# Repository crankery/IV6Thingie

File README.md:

# IV6Thingie

*This does not work yet... It may never work. I'm just goofing around*

When one learns to use a particular 7 segment display, they first make a clock.

I bought a bunch of used IV-6 (ИВ-6) 7 segment display tubes on a whim and they've been sitting in a box for years.

So, I picked out 6 of the cleanest ones and will make a clock.

## Goals

I'm not trying to invent anything new here, I'm just playing with some old electronics parts.

- Use 6 of the 49 tubes I have on hand
- Use a manufactured PCB
- Use a small PCB so it's cheap
- Use available power converter modules rather than futz with that sort of thing
- Use one of these Raspberry PI Picos I have just sitting here
- Excusively use parts that are available from our good pals at AliExpress

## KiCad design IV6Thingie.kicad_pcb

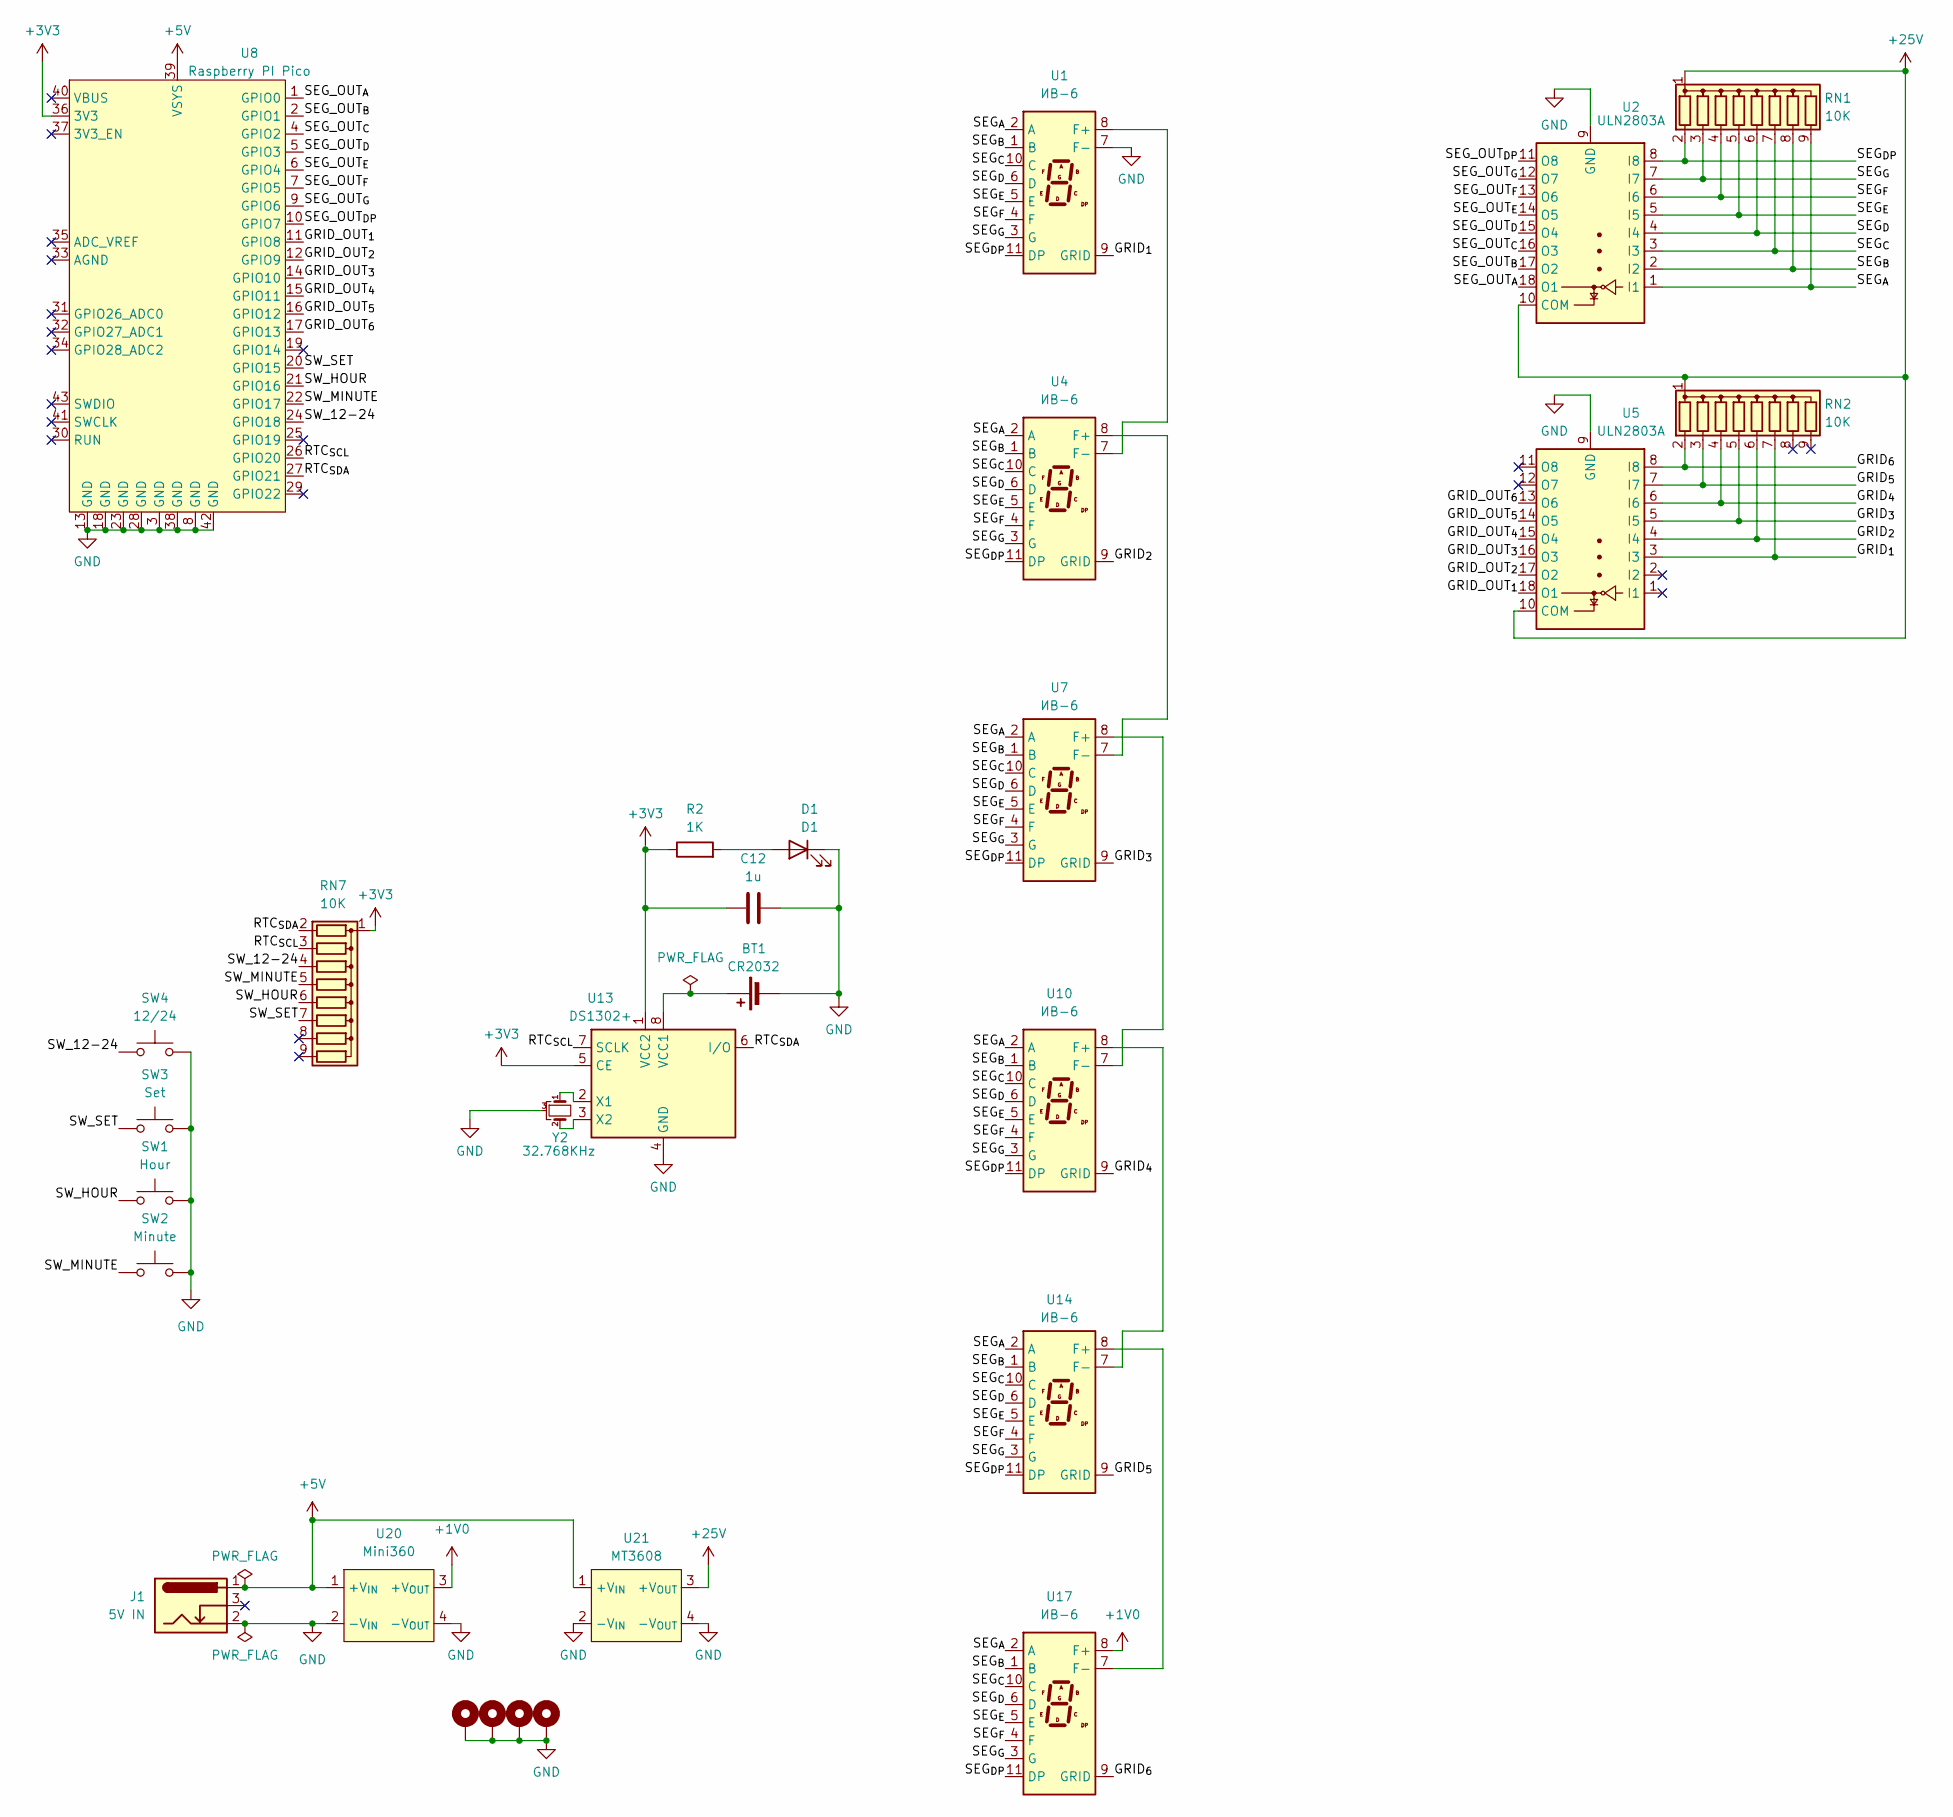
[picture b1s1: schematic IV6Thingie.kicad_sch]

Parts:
BT1: CR2032; BatteryHolder_Myoung_BS-02-Axxx006
C12: 1u; C_Disc_D4.3mm_W1.9mm_P5.00mm
D1: D1; LED_D3.0mm
H1, H2, H3, H4: MountingHole_3.2mm_M3_DIN965_Pad
J1: 5V IN; BarrelJack_Horizontal
R2: 1K; R_Axial_DIN0207_L6.3mm_D2.5mm_P7.62mm_Horizontal
RN1, RN2, RN7: 10K; R_Array_SIP9
SW1: Hour; SW_Tactile_SPST_Angled_PTS645Vx58-2LFS
SW2: Minute; SW_Tactile_SPST_Angled_PTS645Vx58-2LFS
SW3: Set; SW_Tactile_SPST_Angled_PTS645Vx58-2LFS
SW4: 12/24; SW_Tactile_SPST_Angled_PTS645Vx58-2LFS
U1, U4, U7, U10, U14, U17: ИВ-6; IV-6
U2, U5: ULN2803A; DIP-18_W7.62mm
U8: Raspberry PI Pico; RPi_Pico_SMD
U13: DS1302+; DIP-8_W7.62mm
U20: Mini360; Mini360-Module
U21: MT3608; MT3608-Module
Y2: 32.768KHz; Crystal_C26-LF_D2.1mm_L6.5mm_Horizontal_1EP_style2

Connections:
+1V0: U17.8 (F+), U20.3 (+V_{OUT})
+3V3: C12.1, R2.1, RN7.1 (common), U8.36 (3V3), U13.1 (VCC2), U13.5 (CE)
+5V: J1.1, U8.39 (VSYS), U20.1 (+V_{IN}), U21.1 (+V_{IN})
+25V: RN1.1 (common), RN2.1 (common), U2.10 (COM), U5.10 (COM), U21.3 (+V_{OUT})
/GRID_OUT_{1}: U5.18 (O1), U8.11 (GPIO8)
/GRID_OUT_{2}: U5.17 (O2), U8.12 (GPIO9)
/GRID_OUT_{3}: U5.16 (O3), U8.14 (GPIO10)
/GRID_OUT_{4}: U5.15 (O4), U8.15 (GPIO11)
/GRID_OUT_{5}: U5.14 (O5), U8.16 (GPIO12)
/GRID_OUT_{6}: U5.13 (O6), U8.17 (GPIO13)
/GRID_{1}: RN2.7 (R6), U1.9 (GRID), U5.3 (I3)
/GRID_{2}: RN2.6 (R5), U4.9 (GRID), U5.4 (I4)
/GRID_{3}: RN2.5 (R4), U5.5 (I5), U7.9 (GRID)
/GRID_{4}: RN2.4 (R3), U5.6 (I6), U10.9 (GRID)
/GRID_{5}: RN2.3 (R2), U5.7 (I7), U14.9 (GRID)
/GRID_{6}: RN2.2 (R1), U5.8 (I8), U17.9 (GRID)
/RTC_{SCL}: RN7.3 (R2), U8.26 (GPIO20), U13.7 (SCLK)
/RTC_{SDA}: RN7.2 (R1), U8.27 (GPIO21), U13.6 (I/O)
/SEG_OUT_{A}: U2.18 (O1), U8.1 (GPIO0)
/SEG_OUT_{B}: U2.17 (O2), U8.2 (GPIO1)
/SEG_OUT_{C}: U2.16 (O3), U8.4 (GPIO2)
/SEG_OUT_{DP}: U2.11 (O8), U8.10 (GPIO7)
/SEG_OUT_{D}: U2.15 (O4), U8.5 (GPIO3)
/SEG_OUT_{E}: U2.14 (O5), U8.6 (GPIO4)
/SEG_OUT_{F}: U2.13 (O6), U8.7 (GPIO5)
/SEG_OUT_{G}: U2.12 (O7), U8.9 (GPIO6)
/SEG_{A}: RN1.9 (R8), U1.2 (A), U2.1 (I1), U4.2 (A), U7.2 (A), U10.2 (A), U14.2 (A), U17.2 (A)
/SEG_{B}: RN1.8 (R7), U1.1 (B), U2.2 (I2), U4.1 (B), U7.1 (B), U10.1 (B), U14.1 (B), U17.1 (B)
/SEG_{C}: RN1.7 (R6), U1.10 (C), U2.3 (I3), U4.10 (C), U7.10 (C), U10.10 (C), U14.10 (C), U17.10 (C)
/SEG_{DP}: RN1.2 (R1), U1.11 (DP), U2.8 (I8), U4.11 (DP), U7.11 (DP), U10.11 (DP), U14.11 (DP), U17.11 (DP)
/SEG_{D}: RN1.6 (R5), U1.6 (D), U2.4 (I4), U4.6 (D), U7.6 (D), U10.6 (D), U14.6 (D), U17.6 (D)
/SEG_{E}: RN1.5 (R4), U1.5 (E), U2.5 (I5), U4.5 (E), U7.5 (E), U10.5 (E), U14.5 (E), U17.5 (E)
/SEG_{F}: RN1.4 (R3), U1.4 (F), U2.6 (I6), U4.4 (F), U7.4 (F), U10.4 (F), U14.4 (F), U17.4 (F)
/SEG_{G}: RN1.3 (R2), U1.3 (G), U2.7 (I7), U4.3 (G), U7.3 (G), U10.3 (G), U14.3 (G), U17.3 (G)
/SW_12-24: RN7.4 (R3), SW4.2, U8.24 (GPIO18)
/SW_HOUR: RN7.6 (R5), SW1.2, U8.21 (GPIO16)
/SW_MINUTE: RN7.5 (R4), SW2.2, U8.22 (GPIO17)
/SW_SET: RN7.7 (R6), SW3.2, U8.20 (GPIO15)
GND: BT1.2 (-), C12.2, D1.1 (K), H1.1, H2.1, H3.1, H4.1, J1.2, SW1.1, SW2.1, SW3.1, SW4.1, U1.7 (F-), U2.9 (GND), U5.9 (GND), U8.3 (GND), U8.8 (GND), U8.13 (GND), U8.18 (GND), U8.23 (GND), U8.28 (GND), U8.38 (GND), U8.42 (GND), U13.4 (GND), U20.2 (-V_{IN}), U20.4 (-V_{OUT}), U21.2 (-V_{IN}), U21.4 (-V_{OUT}), Y2.3
unnamed: BT1.1 (+), U13.8 (VCC1)
unnamed: D1.2 (A), R2.2
unnamed: U1.8 (F+), U4.7 (F-)
unnamed: U4.8 (F+), U7.7 (F-)
unnamed: U10.8 (F+), U14.7 (F-)
unnamed: U7.8 (F+), U10.7 (F-)
unnamed: U13.2 (X1), Y2.1
unnamed: U13.3 (X2), Y2.2
unnamed: U14.8 (F+), U17.7 (F-)

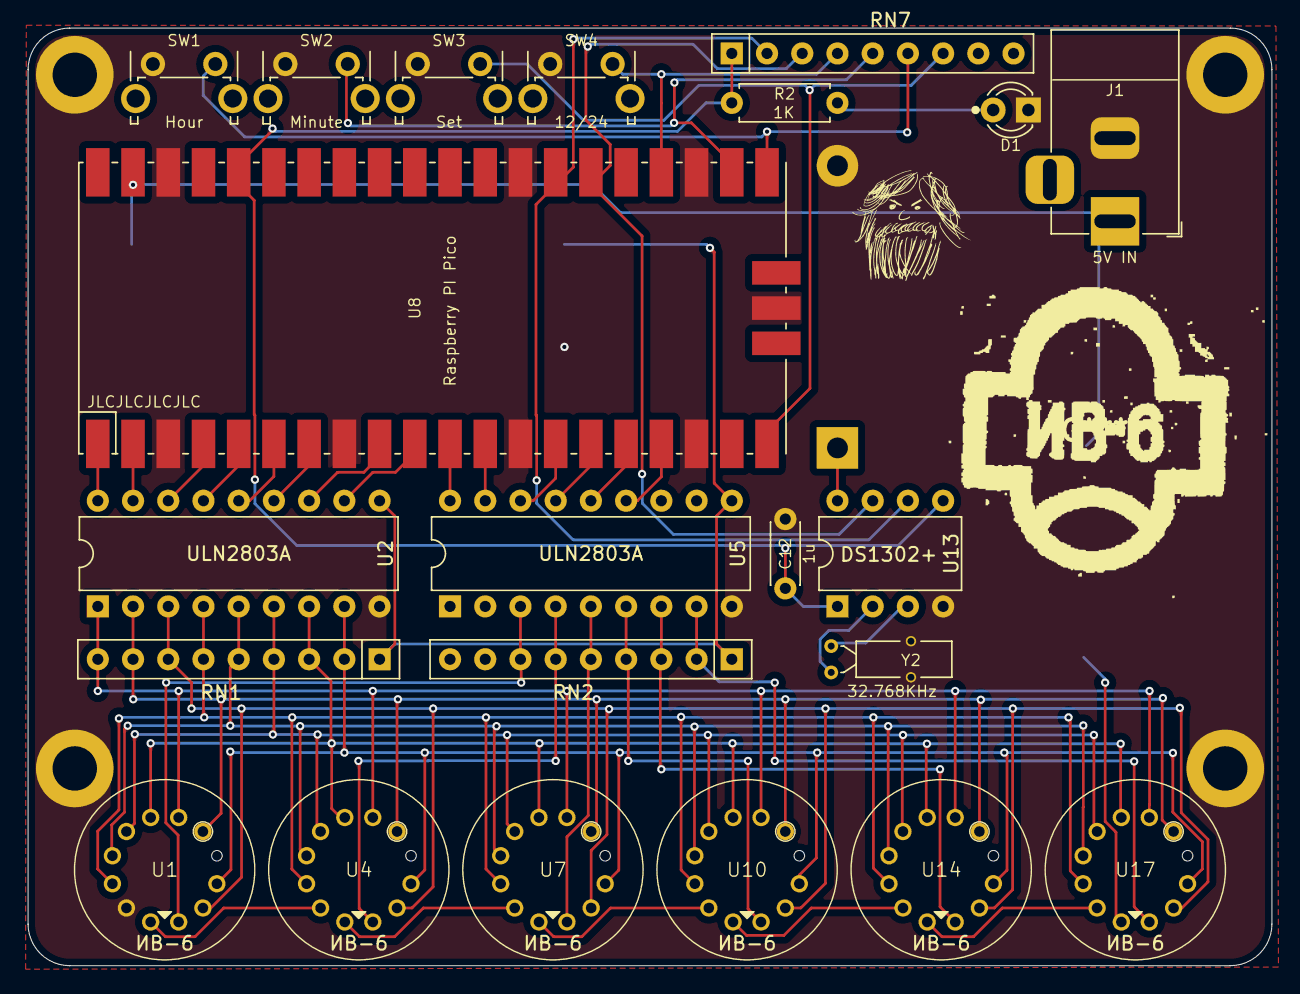
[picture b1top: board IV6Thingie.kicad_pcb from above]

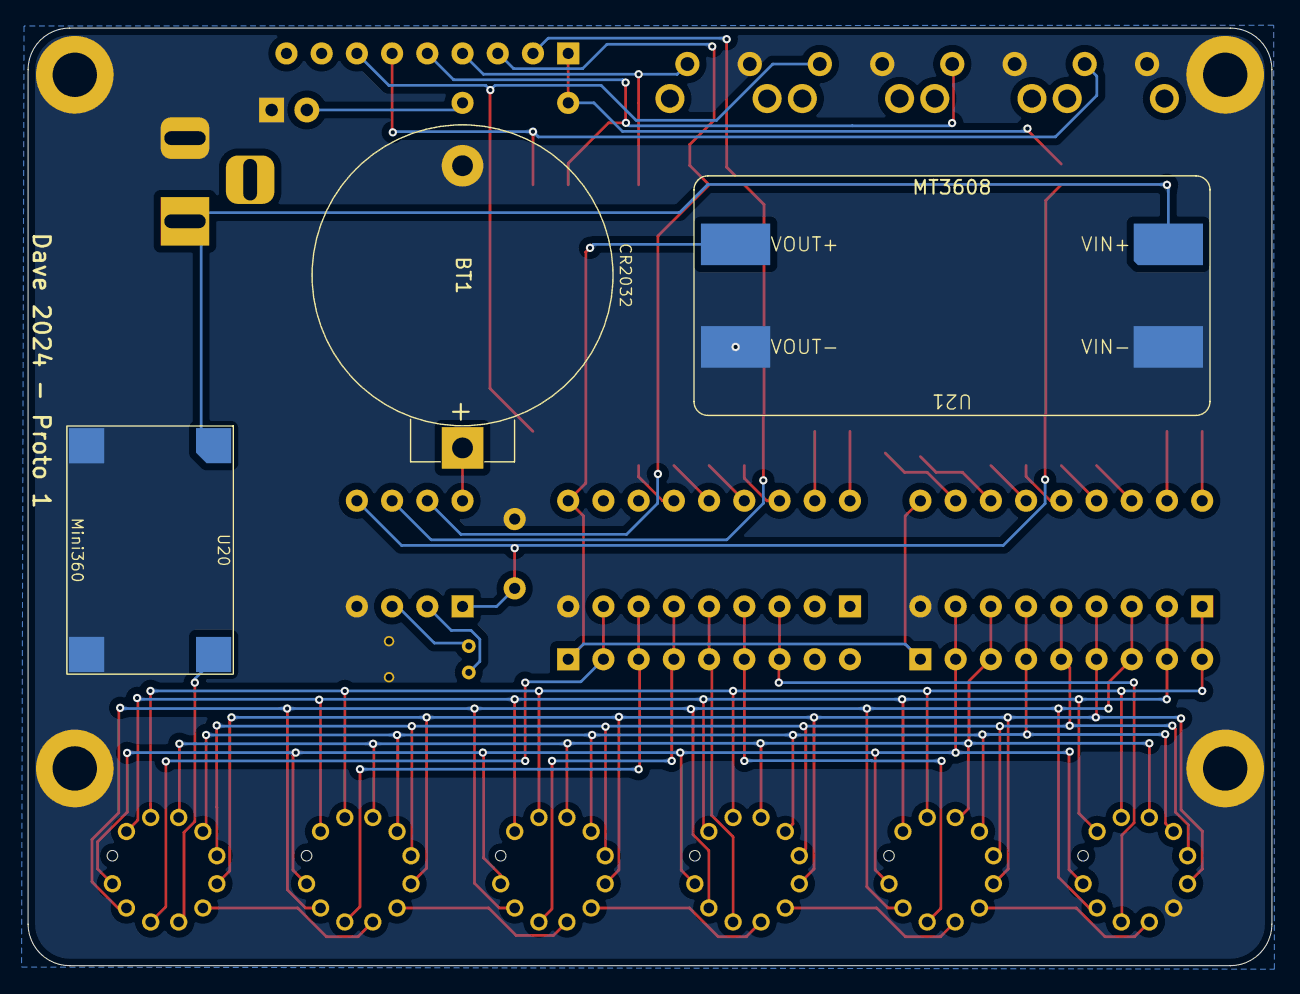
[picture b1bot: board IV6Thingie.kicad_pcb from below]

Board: 2 copper layers, 89.7 x 67.6 mm, 29 parts (3 on the bottom side), 48 nets.

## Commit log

2024-11-03 clean up schema
2024-11-03 nobody cares this is a mac
2024-11-03 start building out the readme and such
